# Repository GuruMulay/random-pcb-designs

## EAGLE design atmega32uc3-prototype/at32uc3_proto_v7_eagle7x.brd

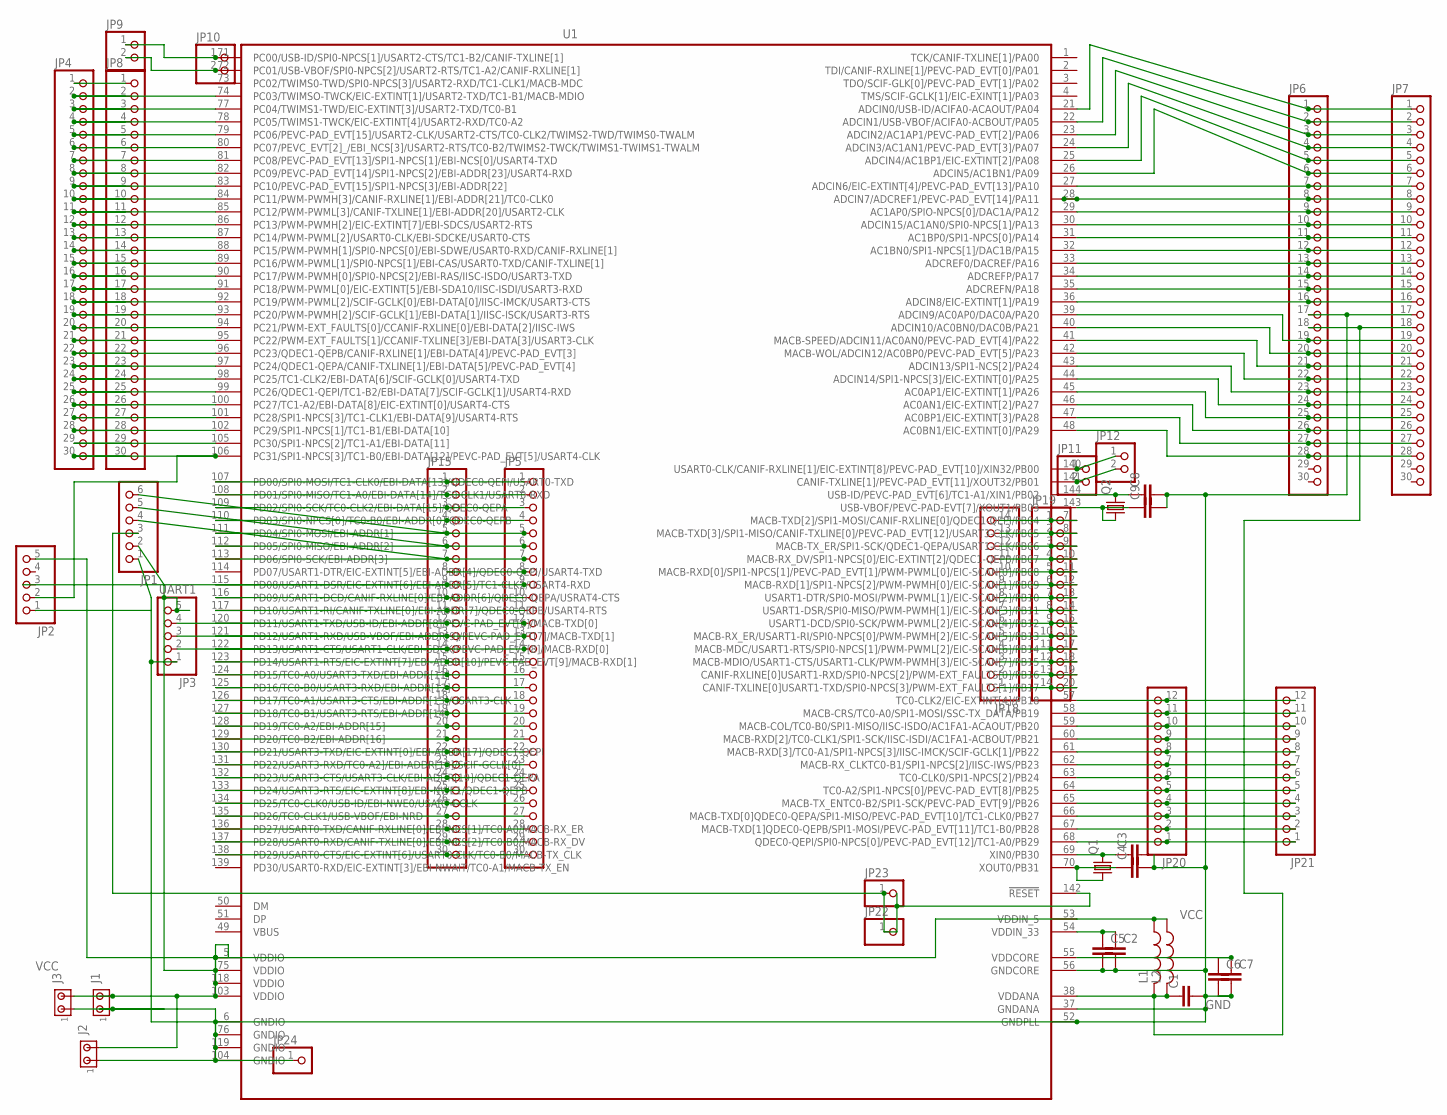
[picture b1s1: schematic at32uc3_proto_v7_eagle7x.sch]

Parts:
C1: C-EU025-050X050; C025-050X050
C2, C3, C4, C5, C6, C7, C8, C9: C-EUC1206K; C1206K
J1, J2, J3: MTA02-100; 10X02MTA
JP1: PINHD-1X6; 1X06
JP2: PINHD-1X5; 1X05
JP3: UART1; 1X05
JP4, JP5, JP6, JP7, JP8, JP15: PINHD-1X30; 1X30
JP9, JP10, JP11, JP12: PINHD-1X2; 1X02
JP18, JP19: PINHD-1X14; 1X14
JP20, JP21: PINHD-1X12; 1X12
JP22, JP23, JP24: PINHD-1X1; 1X01
L1: L-US0207/10; 0207/10
L2: L-USL4532C; L4532M
Q1, Q2: CRYSTALHC49S; HC49/S
U1: AT32UC3C0128/0256/0512; LQFP144

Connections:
GND: C1.2, C2.2, C3.2, C4.2, C5.2, C6.2, C7.2, C8.2, C9.2, J1.1, J2.1, J3.1, JP1.1, JP2.1, JP3.1, JP6.17, JP7.17, JP24.1, U1.6 (GNDIO), U1.37 (GNDANA), U1.52 (GNDPLL), U1.56 (GNDCORE), U1.76 (GNDIO), U1.104 (GNDIO), U1.119 (GNDIO)
unnamed: C2.1, C5.1, U1.54 (VDDIN_33)
unnamed: C4.1, Q1.1, U1.70 (XOUT0/PB31)
unnamed: JP5.8, JP15.8
unnamed: C3.1, Q1.2, U1.69 (XIN0/PB30)
unnamed: C6.1, C7.1, U1.55 (VDDCORE)
unnamed: C8.1, Q2.2, U1.144 (USB-ID/PEVC-PAD_EVT[6]/TC1-A1/XIN1/PB02)
unnamed: C9.1, Q2.1, U1.143 (USB-VBOF/PEVC-PAD-EVT[7]/XOUT1/PB03)
unnamed: JP1.6, JP5.5, JP15.5, U1.111 (PD04/SPI0-MOSI/EBI-ADDR[1])
unnamed: JP1.5, JP5.6, JP15.6, U1.112 (PD05/SPI0-MISO/EBI-ADDR[2])
unnamed: JP1.4, JP5.7, JP15.7, U1.113 (PD06/SPI0-SCK/EBI-ADDR[3])
unnamed: JP1.3, JP22.1, JP23.1, U1.142 (!RESET)
unnamed: JP5.9, JP15.9, U1.115 (PD08/USART1-DSR/EIC-EXTINT[6]/EBI-ADDR[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)
unnamed: JP4.1, JP8.1
unnamed: JP4.2, JP8.2, U1.74 (PC03/TWIMSO-TWCK/EIC-EXTINT[1]/USART2-T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)
unnamed: JP3.4, JP5.12, JP15.12, U1.120 (PD11/USART1-TXD/USB-ID/EBI-ADDR[8]/PEVC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)
unnamed: JP3.3, JP5.13, JP15.13, U1.121 (PD12/USART1-RXD/USB-VBOF/EBI-ADDR[9]/PE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)
unnamed: JP3.2, JP5.14, JP15.14, U1.122 (PD13/USART1-CTS/USART1-CLK/EBI-SDCK/PEV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)
unnamed: JP4.3, JP8.3, U1.77 (PC04/TWIMS1-TWD/EIC-EXTINT[3]/USART2-TX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)
unnamed: JP4.4, JP8.4, U1.78 (PC05/TWIMS1-TWCK/EIC-EXTINT[4]/USART2-R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)
unnamed: JP4.5, JP8.5, U1.79 (PC06/PEVC-PAD_EVT[15]/USART2-CLK/USART2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)
unnamed: JP4.6, JP8.6, U1.80 (PC07/PEVC_EVT[2]_/EBI_NCS[3]/USART2-RTS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)
unnamed: JP4.7, JP8.7, U1.81 (PC08/PEVC-PAD_EVT[13]/SPI1-NPCS[1]/EBI-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)
unnamed: JP4.8, JP8.8, U1.82 (PC09/PEVC-PAD_EVT[14]/SPI1-NPCS[2]/EBI-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)
unnamed: JP4.9, JP8.9, U1.83 (PC10/PEVC-PAD_EVT[15]/SPI1-NPCS[3]/EBI-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)
unnamed: JP4.10, JP8.10, U1.84 (PC11/PWM-PWMH[3]/CANIF-RXLINE[1]/EBI-AD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)
unnamed: JP4.11, JP8.11, U1.85 (PC12/PWM-PWML[3]/CANIF-TXLINE[1]/EBI-AD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)
unnamed: JP4.12, JP8.12, U1.86 (PC13/PWM-PWMH[2]/EIC-EXTINT[7]/EBI-SDCS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)
unnamed: JP4.13, JP8.13, U1.87 (PC14/PWM-PWML[2]/USART0-CLK/EBI-SDCKE/U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)
unnamed: JP4.14, JP8.14, U1.88 (PC15/PWM-PWMH[1]/SPI0-NPCS[0]/EBI-SDWE/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)
unnamed: JP4.15, JP8.15, U1.89 (PC16/PWM-PWML[1]/SPI0-NPCS[1]/EBI-CAS/U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)
unnamed: JP11.1, JP12.1, U1.140 (USART0-CLK/CANIF-RXLINE[1]/EIC-EXTINT[8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)
unnamed: JP4.16, JP8.16, U1.90 (PC17/PWM-PWMH[0]/SPI0-NPCS[2]/EBI-RAS/I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)
unnamed: JP4.17, JP8.17, U1.91 (PC18/PWM-PWML[0]/EIC-EXTINT[5]/EBI-SDA1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)
unnamed: JP4.18, JP8.18, U1.92 (PC19/PWM-PWML[2]/SCIF-GCLK[0]/EBI-DATA[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)
unnamed: JP4.19, JP8.19, U1.93 (PC20/PWM-PWMH[2]/SCIF-GCLK[1]/EBI-DATA[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)
unnamed: JP4.20, JP8.20, U1.94 (PC21/PWM-EXT_FAULTS[0]/CCANIF-RXLINE[0]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)
unnamed: JP4.21, JP8.21, U1.95 (PC22/PWM-EXT_FAULTS[1]/CCANIF-TXLINE[3]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)
unnamed: JP4.22, JP8.22, U1.96 (PC23/QDEC1-QEPB/CANIF-RXLINE[1]/EBI-DAT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)
unnamed: JP4.23, JP8.23, U1.97 (PC24/QDEC1-QEPA/CANIF-TXLINE[1]/EBI-DAT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)
unnamed: JP4.24, JP8.24, U1.98 (PC25/TC1-CLK2/EBI-DATA[6]/SCIF-GCLK[0]/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)
unnamed: JP4.25, JP8.25, U1.99 (PC26/QDEC1-QEPI/TC1-B2/EBI-DATA[7]/SCIF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)
unnamed: JP4.26, JP8.26, U1.100 (PC27/TC1-A2/EBI-DATA[8]/EIC-EXTINT[0]/U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)
unnamed: JP4.27, JP8.27, U1.101 (PC28/SPI1-NPCS[3]/TC1-CLK1/EBI-DATA[9]/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)
unnamed: JP4.28, JP8.28, U1.102 (PC29/SPI1-NPCS[1]/TC1-B1/EBI-DATA[10])
unnamed: JP4.29, JP8.29, U1.105 (PC30/SPI1-NPCS[2]/TC1-A1/EBI-DATA[11])
unnamed: JP2.2, JP4.30, JP8.30, U1.106 (PC31/SPI1-NPCS[3]/TC1-B0/EBI-DATA[12]/P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)
unnamed: JP5.1, JP15.1, U1.107 (PD00/SPI0-MOSI/TC1-CLK0/EBI-DATA[13]/QD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)
unnamed: JP5.2, JP15.2, U1.108 (PD01/SPI0-MISO/TC1-A0/EBI-DATA[14]/TC0-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)
unnamed: JP5.3, JP15.3, U1.109 (PD02/SPI0-SCK/TC0-CLK2/EBI-DATA[15]/QDE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)
unnamed: JP5.4, JP15.4, U1.110 (PD03/SPI0-NPCS[0]/TC0-B0/EBI-ADDR[0]/QD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)
unnamed: JP5.10, JP15.10, U1.116 (PD09/USART1-DCD/CANIF-RXLINE[0]/EBI-ADD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)
unnamed: JP5.11, JP15.11, U1.117 (PD10/USART1-RI/CANIF-TXLINE[0]/EBI-ADDR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)
unnamed: JP5.15, JP15.15, U1.123 (PD14/USART1-RTS/EIC-EXTINT[7]/EBI-ADDR[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)
unnamed: JP5.16, JP15.16, U1.124 (PD15/TC0-A0/USART3-TXD/EBI-ADDR[11])
unnamed: JP5.17, JP15.17, U1.125 (PD16/TC0-B0/USART3-RXD/EBI-ADDR[12])
unnamed: JP5.18, JP15.18, U1.126 (PD17/TC0-A1/USART3-CTS/EBI-ADDR[13]/USA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)
unnamed: JP5.19, JP15.19, U1.127 (PD18/TC0-B1/USART3-RTS/EBI-ADDR[14])
unnamed: JP5.20, JP15.20, U1.128 (PD19/TC0-A2/EBI-ADDR[15])
unnamed: JP5.21, JP15.21, U1.129 (PD20/TC0-B2/EBI-ADDR[16])
unnamed: JP5.22, JP15.22, U1.130 (PD21/USART3-TXD/EIC-EXTINT[0]/EBI-ADDR[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)
unnamed: JP5.23, JP15.23, U1.131 (PD22/USART3-RXD/TC0-A2]/EBI-ADDR[18]/SC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)
unnamed: JP5.24, JP15.24, U1.132 (PD23/USART3-CTS/USART3-CLK/EBI-ADDR[19]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)
unnamed: JP5.25, JP15.25, U1.133 (PD24/USART3-RTS/EIC-EXTINT[8]/EBI-NWE1/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)
unnamed: JP5.26, JP15.26, U1.134 (PD25/TC0-CLK0/USB-ID/EBI-NWE0/USART4-CLK)
unnamed: JP5.27, JP15.27, U1.135 (PD26/TC0-CLK1/USB-VBOF/EBI-NRD)
unnamed: JP5.28, JP15.28, U1.136 (PD27/USART0-TXD/CANIF-RXLINE[0]/EBI-NCS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)
unnamed: JP5.29, JP15.29, U1.137 (PD28/USART0-RXD/CANIF-TXLINE[0]/EBI-NCS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)
unnamed: JP5.30, JP15.30, U1.138 (PD29/USART0-CTS/EIC-EXTINT[6]/USART0-CL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)
unnamed: JP9.1, JP10.1, U1.71 (PC00/USB-ID/SPI0-NPCS[1]/USART2-CTS/TC1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)
unnamed: JP6.1, JP7.1, U1.21 (ADCIN0/USB-ID/ACIFA0-ACAOUT/PA04)
unnamed: JP6.2, JP7.2, U1.22 (ADCIN1/USB-VBOF/ACIFA0-ACBOUT/PA05)
unnamed: JP6.3, JP7.3, U1.23 (ADCIN2/AC1AP1/PEVC-PAD_EVT[2]/PA06)
unnamed: JP6.4, JP7.4, U1.24 (ADCIN3/AC1AN1/PEVC-PAD_EVT[3]/PA07)
unnamed: JP6.5, JP7.5, U1.25 (ADCIN4/AC1BP1/EIC-EXTINT[2]/PA08)
unnamed: JP6.6, JP7.6, U1.26 (ADCIN5/AC1BN1/PA09)
unnamed: JP6.9, JP7.9, U1.29 (AC1AP0/SPIO-NPCS[0]/DAC1A/PA12)
unnamed: JP6.8, JP7.8, U1.28 (ADCIN7/ADCREF1/PEVC-PAD_EVT[14]/PA11)
unnamed: JP6.7, JP7.7, U1.27 (ADCIN6/EIC-EXTINT[4]/PEVC-PAD_EVT[13]/P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)
unnamed: JP6.10, JP7.10, U1.30 (ADCIN15/AC1AN0/SPI0-NPCS[1]/PA13)
unnamed: JP6.11, JP7.11, U1.31 (AC1BP0/SPI1-NPCS[0]/PA14)
unnamed: JP6.12, JP7.12, U1.32 (AC1BN0/SPI1-NPCS[1]/DAC1B/PA15)
unnamed: JP6.13, JP7.13, U1.33 (ADCREF0/DACREF/PA16)
unnamed: JP6.14, JP7.14, U1.34 (ADCREFP/PA17)
unnamed: JP6.15, JP7.15, U1.35 (ADCREFN/PA18)
unnamed: JP6.16, JP7.16, U1.36 (ADCIN8/EIC-EXTINT[1]/PA19)
unnamed: JP6.19, JP7.19, U1.39 (ADCIN9/AC0AP0/DAC0A/PA20)
unnamed: JP6.20, JP7.20, U1.40 (ADCIN10/AC0BN0/DAC0B/PA21)
unnamed: JP6.21, JP7.21, U1.41 (MACB-SPEED/ADCIN11/AC0AN0/PEVC-PAD_EVT[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)
unnamed: JP6.22, JP7.22, U1.42 (MACB-WOL/ADCIN12/AC0BP0/PEVC-PAD_EVT[5]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)
unnamed: JP6.23, JP7.23, U1.43 (ADCIN13/SPI1-NCS[2]/PA24)
unnamed: JP6.24, JP7.24, U1.44 (ADCIN14/SPI1-NPCS[3]/EIC-EXTINT[0]/PA25)
unnamed: JP6.25, JP7.25, U1.45 (AC0AP1/EIC-EXTINT[1]/PA26)
unnamed: JP6.26, JP7.26, U1.46 (AC0AN1/EIC-EXTINT[2]/PA27)
unnamed: JP6.27, JP7.27, U1.47 (AC0BP1/EIC-EXTINT[3]/PA28)
unnamed: JP6.28, JP7.28, U1.48 (AC0BN1/EIC-EXTINT[0]/PA29)
unnamed: JP9.2, JP10.2, U1.72 (PC01/USB-VBOF/SPI0-NPCS[2]/USART2-RTS/T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)
unnamed: JP11.2, JP12.2, U1.141 (CANIF-TXLINE[1]/PEVC-PAD_EVT[11]/XOUT32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)
unnamed: JP18.1, JP19.14, U1.20 (CANIF-TXLINE[0]USART1-TXD/SPI0-NPCS[3]/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)
unnamed: JP18.2, JP19.13, U1.19 (CANIF-RXLINE[0]USART1-RXD/SPI0-NPCS[2]/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)
unnamed: JP18.3, JP19.12, U1.18 (MACB-MDIO/USART1-CTS/USART1-CLK/PWM-PWM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)
unnamed: JP18.4, JP19.11, U1.17 (MACB-MDC/USART1-RTS/SPI0-NPCS[1]/PWM-PW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)
unnamed: JP18.5, JP19.10, U1.16 (MACB-RX_ER/USART1-RI/SPI0-NPCS[0]/PWM-P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)
unnamed: JP18.6, JP19.9, U1.15 (USART1-DCD/SPI0-SCK/PWM-PWML[2]/EIC-SCA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)
unnamed: JP18.7, JP19.8, U1.14 (USART1-DSR/SPI0-MISO/PWM-PWMH[1]/EIC-SC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)
unnamed: JP18.8, JP19.7, U1.13 (USART1-DTR/SPI0-MOSI/PWM-PWML[1]/EIC-SC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)
unnamed: JP18.9, JP19.6, U1.12 (MACB-RXD[1]/SPI1-NPCS[2]/PWM-PWMH[0]/EI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)
unnamed: JP18.10, JP19.5, U1.11 (MACB-RXD[0]/SPI1-NPCS[1]/PEVC-PAD_EVT[1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)
unnamed: JP18.11, JP19.4, U1.10 (MACB-RX_DV/SPI1-NPCS[0]/EIC-EXTINT[2]/Q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)
unnamed: JP18.12, JP19.3, U1.9 (MACB-TX_ER/SPI1-SCK/QDEC1-QEPA/USART1-C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)
unnamed: JP18.13, JP19.2, U1.8 (MACB-TXD[3]/SPI1-MISO/CANIF-TXLINE[0]/P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)
unnamed: JP18.14, JP19.1, U1.7 (MACB-TXD[2]/SPI1-MOSI/CANIF-RXLINE[0]/Q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)
unnamed: JP20.1, JP21.1, U1.68 (QDEC0-QEPI/SPI0-NPCS[0]/PEVC-PAD_EVT[12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)
unnamed: JP20.2, JP21.2, U1.67 (MACB-TXD[1]QDEC0-QEPB/SPI1-MOSI/PEVC-PA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)
unnamed: JP20.3, JP21.3, U1.66 (MACB-TXD[0]QDEC0-QEPA/SPI1-MISO/PEVC-PA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)
unnamed: JP20.4, JP21.4, U1.65 (MACB-TX_ENTC0-B2/SPI1-SCK/PEVC-PAD_EVT[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)
unnamed: JP20.5, JP21.5, U1.64 (TC0-A2/SPI1-NPCS[0]/PEVC-PAD_EVT[8]/PB25)
unnamed: JP20.6, JP21.6, U1.63 (TC0-CLK0/SPI1-NPCS[2]/PB24)
unnamed: JP20.7, JP21.7, U1.62 (MACB-RX_CLKTC0-B1/SPI1-NPCS[2]/IISC-IWS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)
unnamed: JP20.8, JP21.8, U1.61 (MACB-RXD[3]/TC0-A1/SPI1-NPCS[3]/IISC-IM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)
unnamed: JP20.9, JP21.9, U1.60 (MACB-RXD[2]/TC0-CLK1/SPI1-SCK/IISC-ISDI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)
unnamed: JP20.10, JP21.10, U1.59 (MACB-COL/TC0-B0/SPI1-MISO/IISC-ISDO/AC1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)
unnamed: JP20.11, JP21.11, U1.58 (MACB-CRS/TC0-A0/SPI1-MOSI/SSC-TX_DATA/P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)
unnamed: JP20.12, JP21.12, U1.57 (TC0-CLK2/EIC-EXTINT[4]/PB18)
unnamed: C1.1, JP6.18, JP7.18, L1.2, L2.2, U1.38 (VDDANA)
VCC: J1.2, J2.2, J3.2, JP1.2, JP2.5, JP3.5, L1.1, L2.1, U1.5 (VDDIO), U1.53 (VDDIN_5), U1.75 (VDDIO), U1.103 (VDDIO), U1.118 (VDDIO)

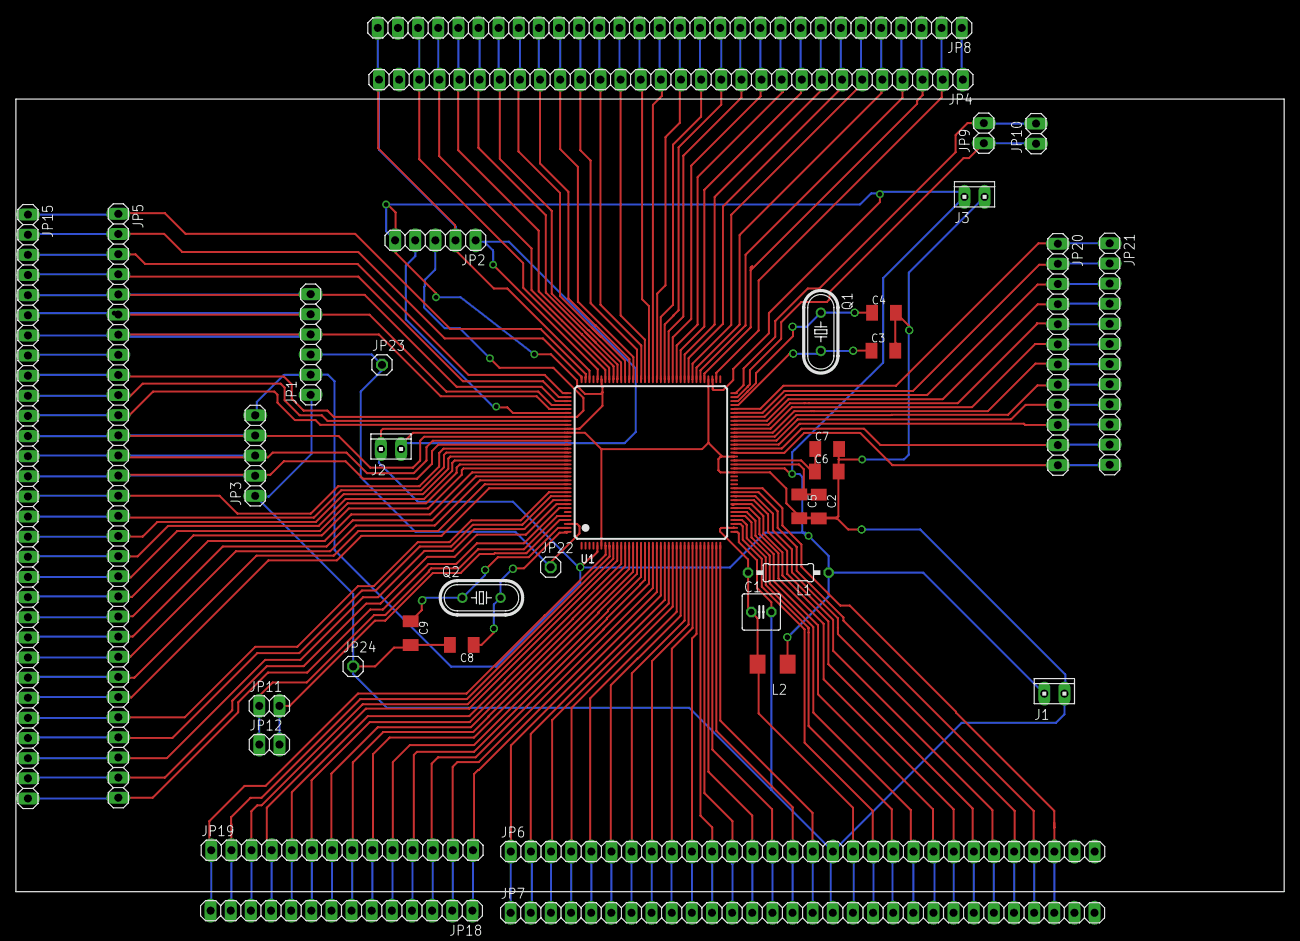
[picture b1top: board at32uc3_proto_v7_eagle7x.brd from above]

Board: 2 copper layers, 160.0 x 100.0 mm, 37 parts (0 on the bottom side), 126 nets.

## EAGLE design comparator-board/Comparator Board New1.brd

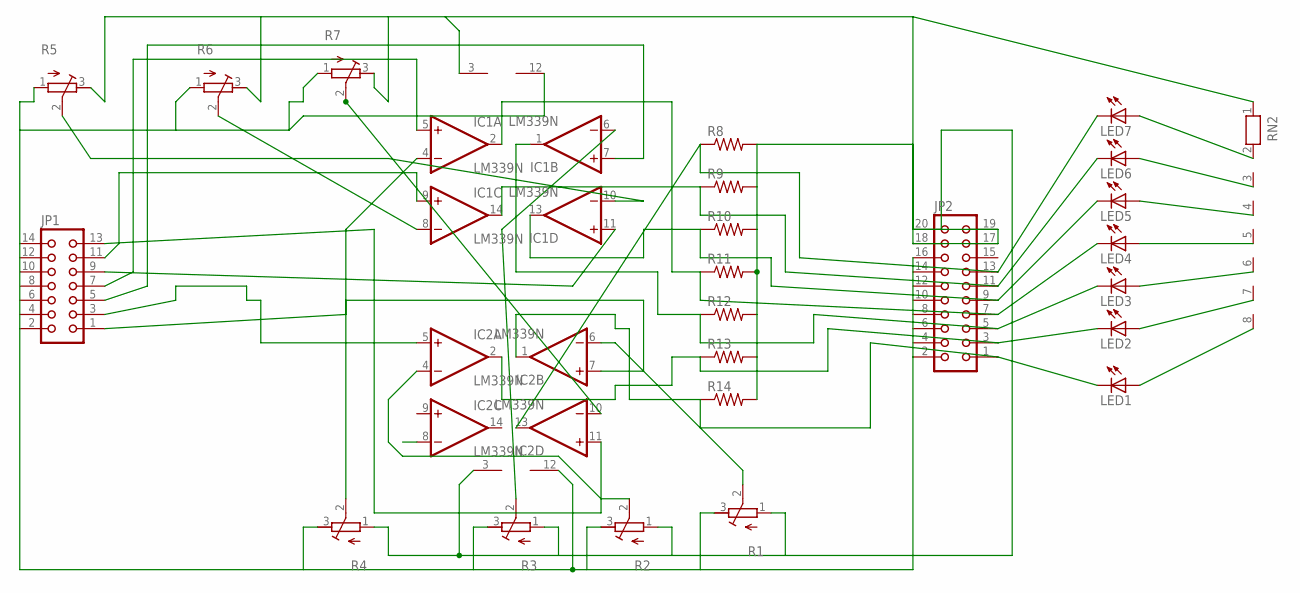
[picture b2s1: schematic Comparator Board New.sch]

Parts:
IC1, IC2: LM339N; DIL14
JP1: CON14
JP2: CON20
LED1, LED2, LED3, LED4, LED5, LED6, LED7: LED3MM
R1, R2, R3, R4, R5, R6, R7: R-TRIMM3296W; RTRIM3296W
R8, R9, R10, R11, R12, R13, R14: R-US_0207/15; 0207/15
RN2: RN07; RN-8

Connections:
unnamed: IC2.7 (+IN), JP1.1
unnamed: IC1.7 (+IN), JP1.5
unnamed: IC1.5 (+IN), JP1.7
unnamed: IC1.11 (+IN), JP1.9
unnamed: IC1.9 (+IN), JP1.11
unnamed: IC2.13 (OUT), JP2.13, LED7.K (C), R8.1
unnamed: IC2.11 (+IN), JP1.13
unnamed: IC2.5 (+IN), JP1.3
unnamed: IC1.14 (OUT), JP2.11, LED6.K (C), R9.1
unnamed: IC2.1 (OUT), JP2.1, LED1.K (C), R14.1
unnamed: IC2.2 (OUT), JP2.3, LED2.K (C), R13.1
unnamed: LED7.A, RN2.2
unnamed: IC1.12 (GND), IC2.12 (GND), JP1.2, JP1.4, JP1.6, JP1.8, JP1.10, JP1.12, JP1.14, JP2.2, JP2.4, JP2.6, JP2.8, JP2.10, JP2.12, JP2.14, JP2.16, R1.3 (A), R2.3 (A), R3.3 (A), R4.3 (A), R5.1 (E), R6.1 (E), R7.1 (E)
unnamed: LED6.A, RN2.3
unnamed: LED5.A, RN2.4
unnamed: IC1.1 (OUT), JP2.5, LED3.K (C), R12.1
unnamed: IC1.2 (OUT), JP2.7, LED4.K (C), R11.1
unnamed: IC1.13 (OUT), JP2.9, LED5.K (C), R10.1
unnamed: LED4.A, RN2.5
unnamed: LED3.A, RN2.6
unnamed: LED2.A, RN2.7
unnamed: LED1.A, RN2.8
unnamed: IC2.6 (-IN), R1.2 (S)
unnamed: IC2.4 (-IN), R2.2 (S)
unnamed: IC1.6 (-IN), R3.2 (S)
unnamed: IC1.4 (-IN), R4.2 (S)
unnamed: IC1.10 (-IN), R5.2 (S)
unnamed: IC1.8 (-IN), R6.2 (S)
unnamed: IC2.10 (-IN), R7.2 (S)
unnamed: IC1.3 (V+), IC2.3 (V+), JP2.17, JP2.18, JP2.19, JP2.20, R1.1 (E), R2.1 (E), R3.1 (E), R4.1 (E), R5.3 (A), R6.3 (A), R7.3 (A), R8.2, R9.2, R10.2, R11.2, R12.2, R13.2, R14.2, RN2.1

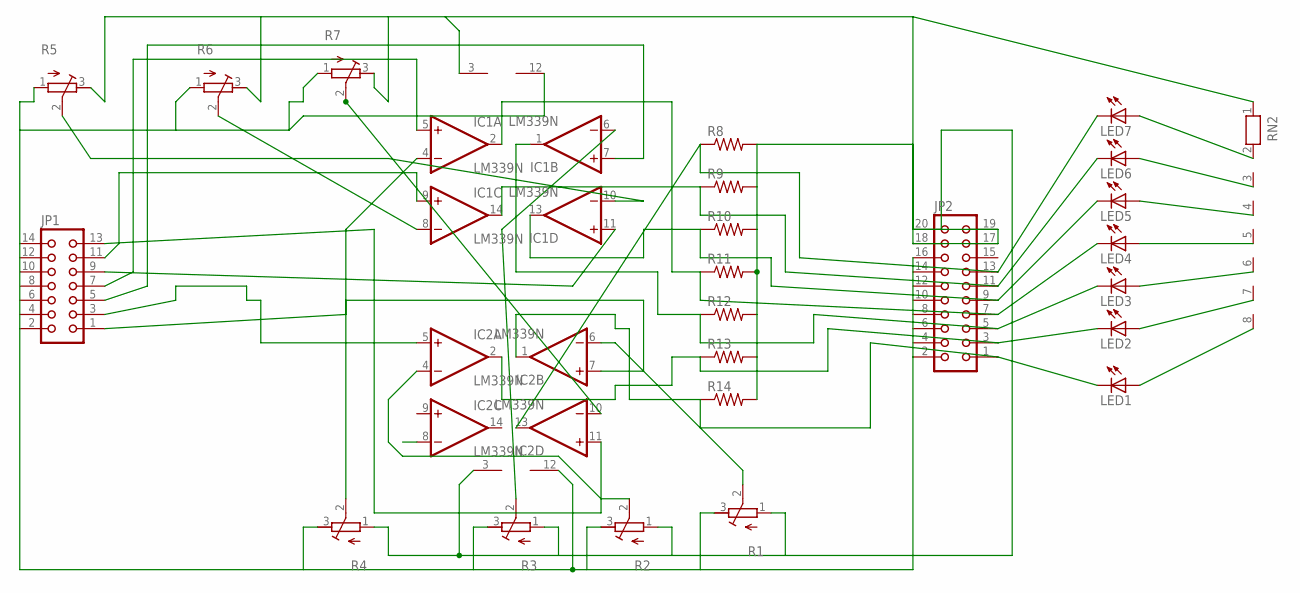
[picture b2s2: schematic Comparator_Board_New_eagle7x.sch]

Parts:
IC1, IC2: LM339N; DIL14
JP1: CON14
JP2: CON20
LED1, LED2, LED3, LED4, LED5, LED6, LED7: LED3MM
R1, R2, R3, R4, R5, R6, R7: R-TRIMM3296W; RTRIM3296W
R8, R9, R10, R11, R12, R13, R14: R-US_0207/15; 0207/15
RN2: RN07; RN-8

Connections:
unnamed: IC2.7 (+IN), JP1.1
unnamed: IC1.7 (+IN), JP1.5
unnamed: IC1.5 (+IN), JP1.7
unnamed: IC1.11 (+IN), JP1.9
unnamed: IC1.9 (+IN), JP1.11
unnamed: IC2.13 (OUT), JP2.13, LED7.K (C), R8.1
unnamed: IC2.11 (+IN), JP1.13
unnamed: IC2.5 (+IN), JP1.3
unnamed: IC1.14 (OUT), JP2.11, LED6.K (C), R9.1
unnamed: IC2.1 (OUT), JP2.1, LED1.K (C), R14.1
unnamed: IC2.2 (OUT), JP2.3, LED2.K (C), R13.1
unnamed: LED7.A, RN2.2
unnamed: IC1.12 (GND), IC2.12 (GND), JP1.2, JP1.4, JP1.6, JP1.8, JP1.10, JP1.12, JP1.14, JP2.2, JP2.4, JP2.6, JP2.8, JP2.10, JP2.12, JP2.14, JP2.16, R1.3 (A), R2.3 (A), R3.3 (A), R4.3 (A), R5.1 (E), R6.1 (E), R7.1 (E)
unnamed: LED6.A, RN2.3
unnamed: LED5.A, RN2.4
unnamed: IC1.1 (OUT), JP2.5, LED3.K (C), R12.1
unnamed: IC1.2 (OUT), JP2.7, LED4.K (C), R11.1
unnamed: IC1.13 (OUT), JP2.9, LED5.K (C), R10.1
unnamed: LED4.A, RN2.5
unnamed: LED3.A, RN2.6
unnamed: LED2.A, RN2.7
unnamed: LED1.A, RN2.8
unnamed: IC2.6 (-IN), R1.2 (S)
unnamed: IC2.4 (-IN), R2.2 (S)
unnamed: IC1.6 (-IN), R3.2 (S)
unnamed: IC1.4 (-IN), R4.2 (S)
unnamed: IC1.10 (-IN), R5.2 (S)
unnamed: IC1.8 (-IN), R6.2 (S)
unnamed: IC2.10 (-IN), R7.2 (S)
unnamed: IC1.3 (V+), IC2.3 (V+), JP2.17, JP2.18, JP2.19, JP2.20, R1.1 (E), R2.1 (E), R3.1 (E), R4.1 (E), R5.3 (A), R6.3 (A), R7.3 (A), R8.2, R9.2, R10.2, R11.2, R12.2, R13.2, R14.2, RN2.1

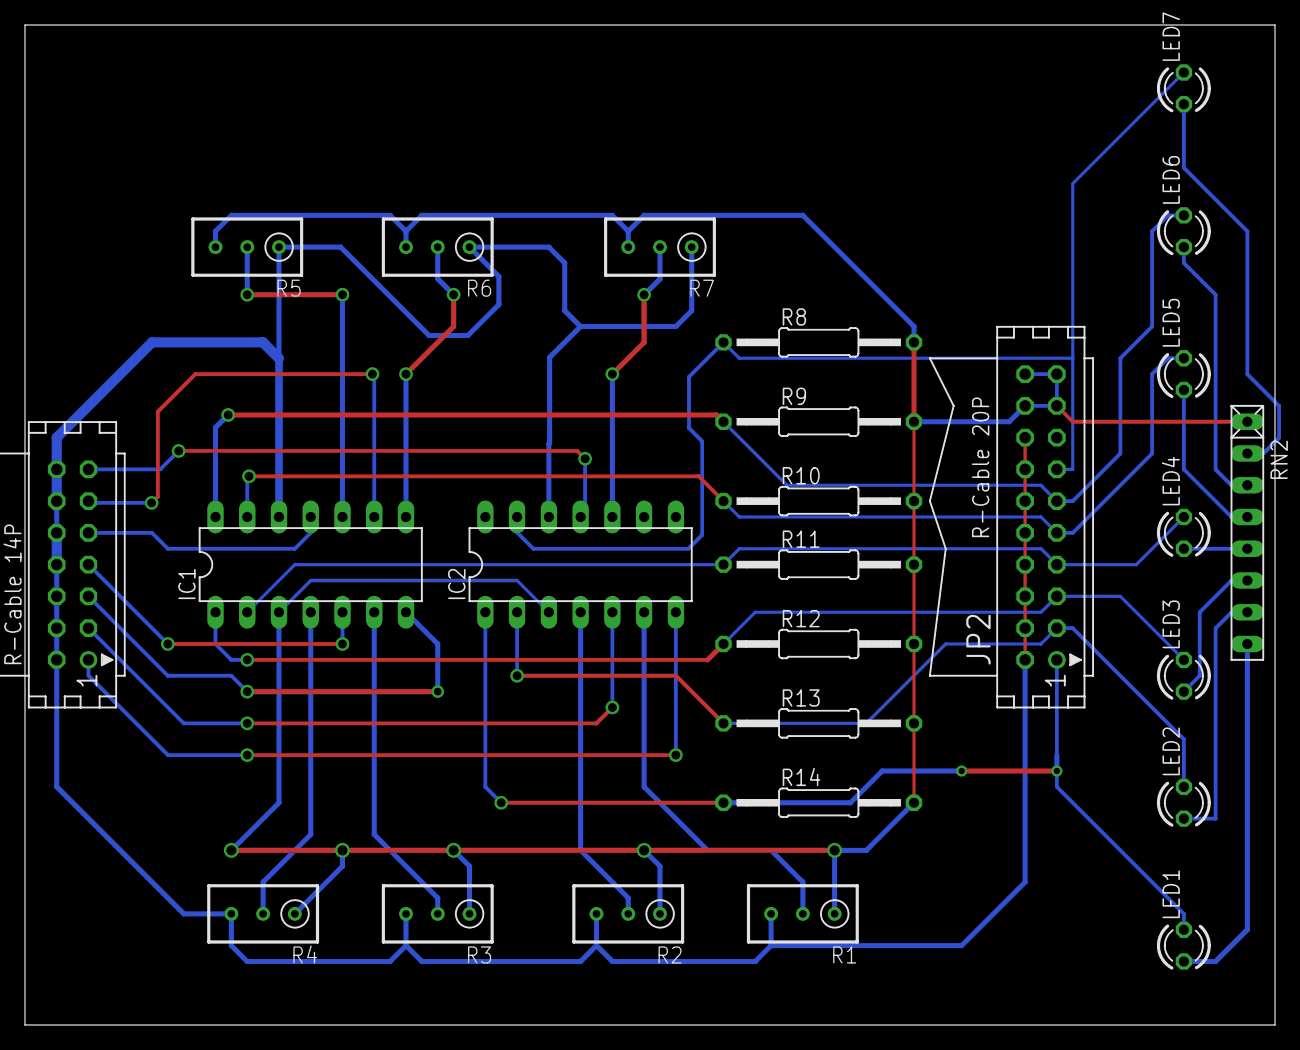
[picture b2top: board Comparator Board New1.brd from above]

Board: 2 copper layers, 100.0 x 80.0 mm, 26 parts (0 on the bottom side), 30 nets.
